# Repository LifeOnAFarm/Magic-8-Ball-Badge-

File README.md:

# Magic 8-Ball Badge 
Created in the lead up to DefCon 26 #BadgeLife

## Getting Started

Welcome to the Magic 8-Ball Badge files/guide.

Here you will find a svg image of the PCB and all the schematics, gerbers and Kicad files you need to make your own Magic 8-Ball Badge. I recommend @MrTwinkleTwink's video on how to convert svg images to Kicad files using Inkscape if you want to make any board chances (https://youtu.be/61NFK9KW).
  
First off, as a warning, I'm by no stretch of the imagination a professional PCB designer and while I have tested the circuit on a similar project I've yet to receive and test this PCB (Will update when I do). Make sure to check through the schematics and make any changes you feel fit (and try not to have an aneurysm when you look at my wiring).

## Quirks:

There are a few quirks to this board. One ~~flaw~~ feature is that the switch doesn't power the PCB on and off, but switches the power from the 8-Ball circuit to the Shitty Add-On headers. Another quirk you might notice in Kicad, is that I couldn't find the footprint for a SW-200D tilt switch so I just used a similar sized component.

## Components You Will Need:

- 1 x SW-200D Tilt Switch

- 3 x 0.1" 2x2 Female Headers

- 8 x 1206 LEDS (Solder these with the top of the LED facing towards the PCB board)

- 1 x Keystone 1058 2032 Coincell Battery Holder

- 1 x CD4017BM Decade counter

- 1 x 0805 10K Resistor

- 1 x 0805 220 Resistor

- 1 x Switch Slide JS202011SCQN 

## Authors

- Seamus de Cleir (@PotatoNightmare)

## License

This project is licensed under the MIT License. 

All I ask is that you leave my Twitter handle on the back of the board, thanks. - see the LICENSE.md file for more details

## Acknowledgments

@MrTwinkleTwink for the great tutorial on SAO's 

## Donations

A button to buy me a cup of coffee if you see fit

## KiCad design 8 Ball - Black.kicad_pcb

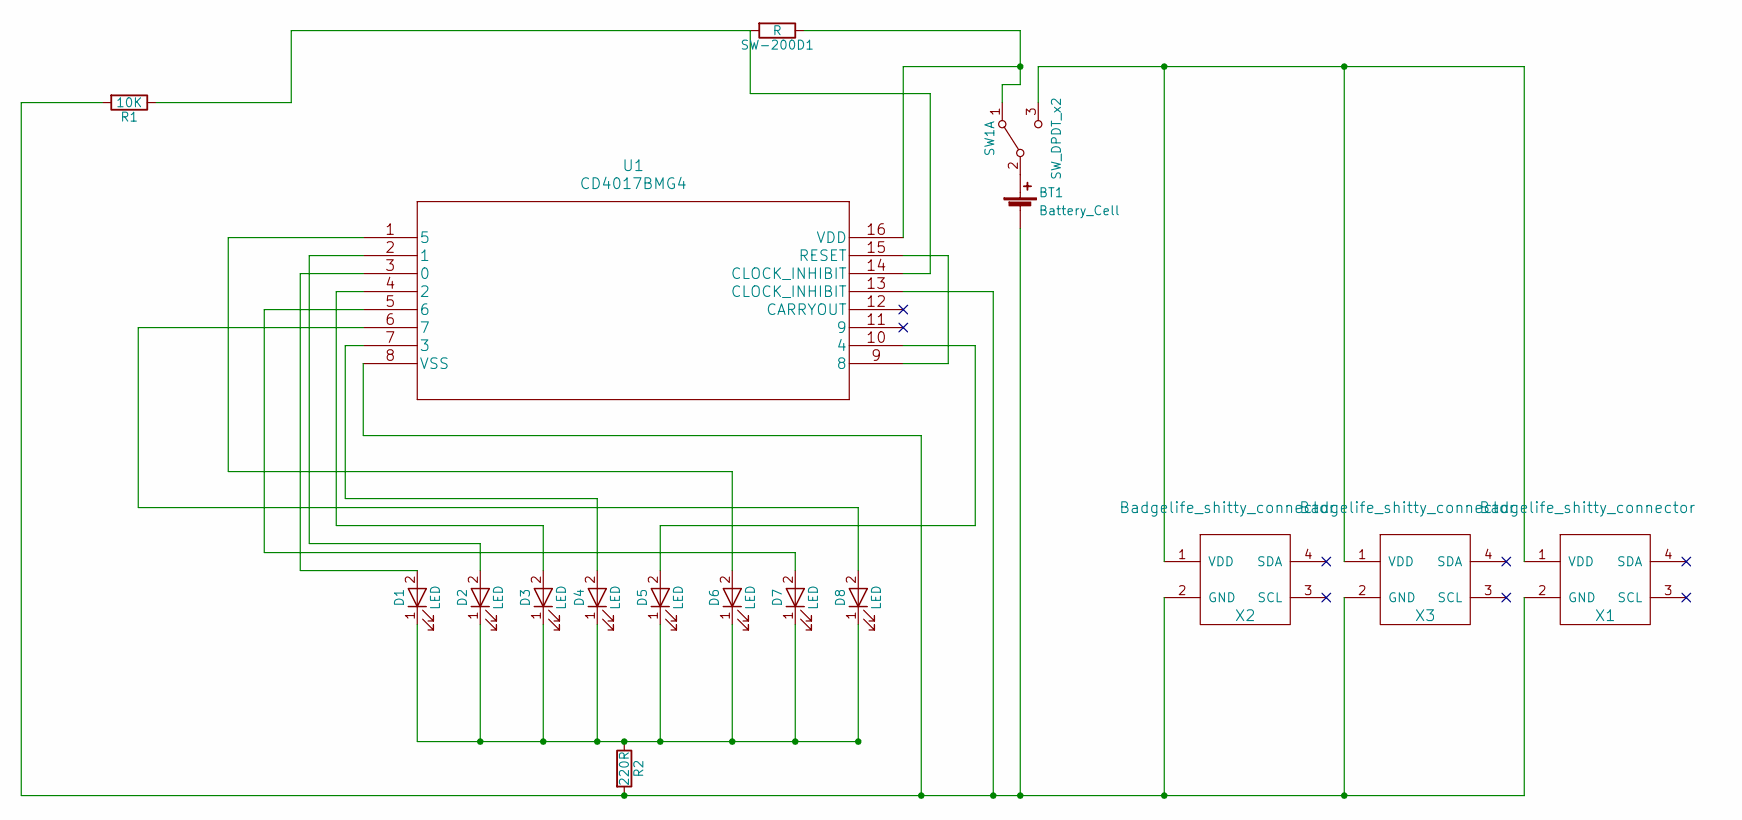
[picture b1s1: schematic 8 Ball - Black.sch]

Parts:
BT1: Battery_Cell; Keystone_1058_1x2032-CoinCell
D1, D2, D3, D4, D5, D6, D7, D8: LED; LED_1206_HandSoldering
R1: 10K; LED_0805_HandSoldering
R2: 220R; LED_0805_HandSoldering
SW1: SW_DPDT_x2; Switch_Slide_JS202011SCQN
SW-200D1: R; CP_Axial_L10.0mm_D4.5mm_P15.00mm_Horizontal
U1: CD4017BMG4; CD4017BM96
X1, X2, X3: Badgelife_shitty_connector; Badgelife-Shitty-2x2

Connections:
unnamed: BT1.1 (+), SW1.2 (B)
unnamed: BT1.2 (-), R1.2, R2.2, U1.8 (VSS), U1.13 (CLOCK_INHIBIT), X1.2 (GND), X2.2 (GND), X3.2 (GND)
unnamed: D1.1 (K), D2.1 (K), D3.1 (K), D4.1 (K), D5.1 (K), D6.1 (K), D7.1 (K), D8.1 (K), R2.1
unnamed: D1.2 (A), U1.3 (0)
unnamed: D2.2 (A), U1.2 (1)
unnamed: D3.2 (A), U1.4 (2)
unnamed: D4.2 (A), U1.7 (3)
unnamed: D5.2 (A), U1.10 (4)
unnamed: D6.2 (A), U1.1 (5)
unnamed: D7.2 (A), U1.5 (6)
unnamed: D8.2 (A), U1.6 (7)
unnamed: R1.1, SW-200D1.2, U1.14 (CLOCK_INHIBIT)
unnamed: SW1.3 (C), X1.1 (VDD), X2.1 (VDD), X3.1 (VDD)
unnamed: SW1.1 (A), SW-200D1.1, U1.16 (VDD)
unnamed: U1.9 (8), U1.15 (RESET)

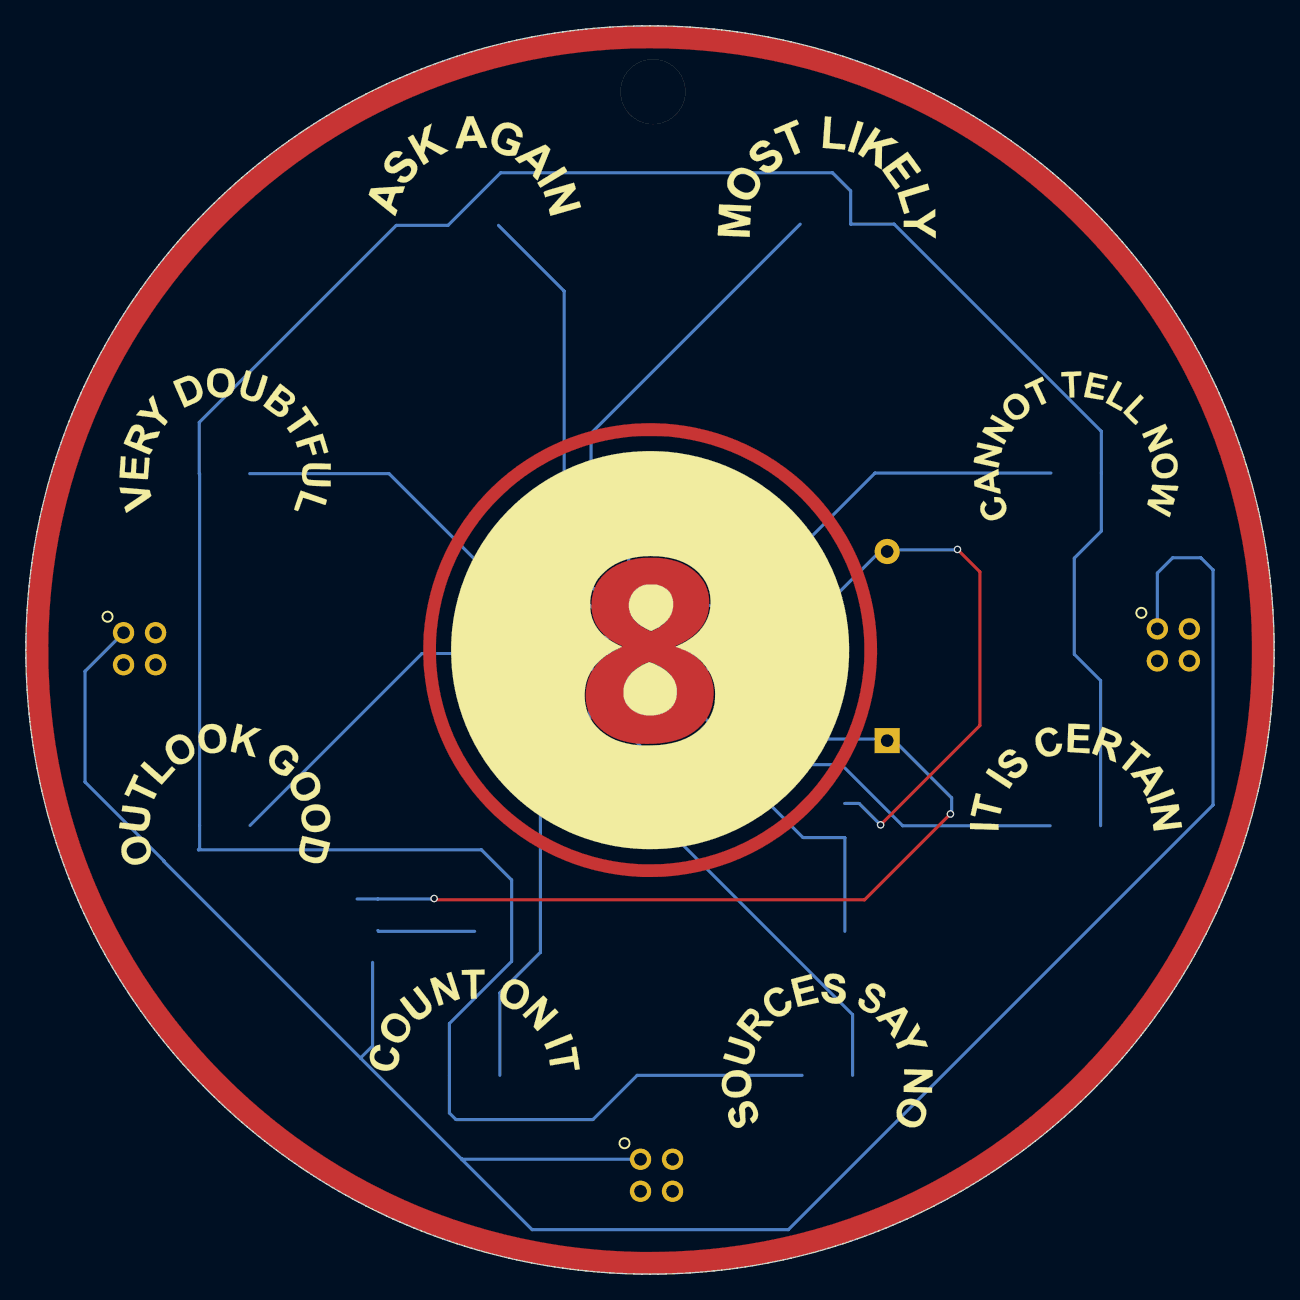
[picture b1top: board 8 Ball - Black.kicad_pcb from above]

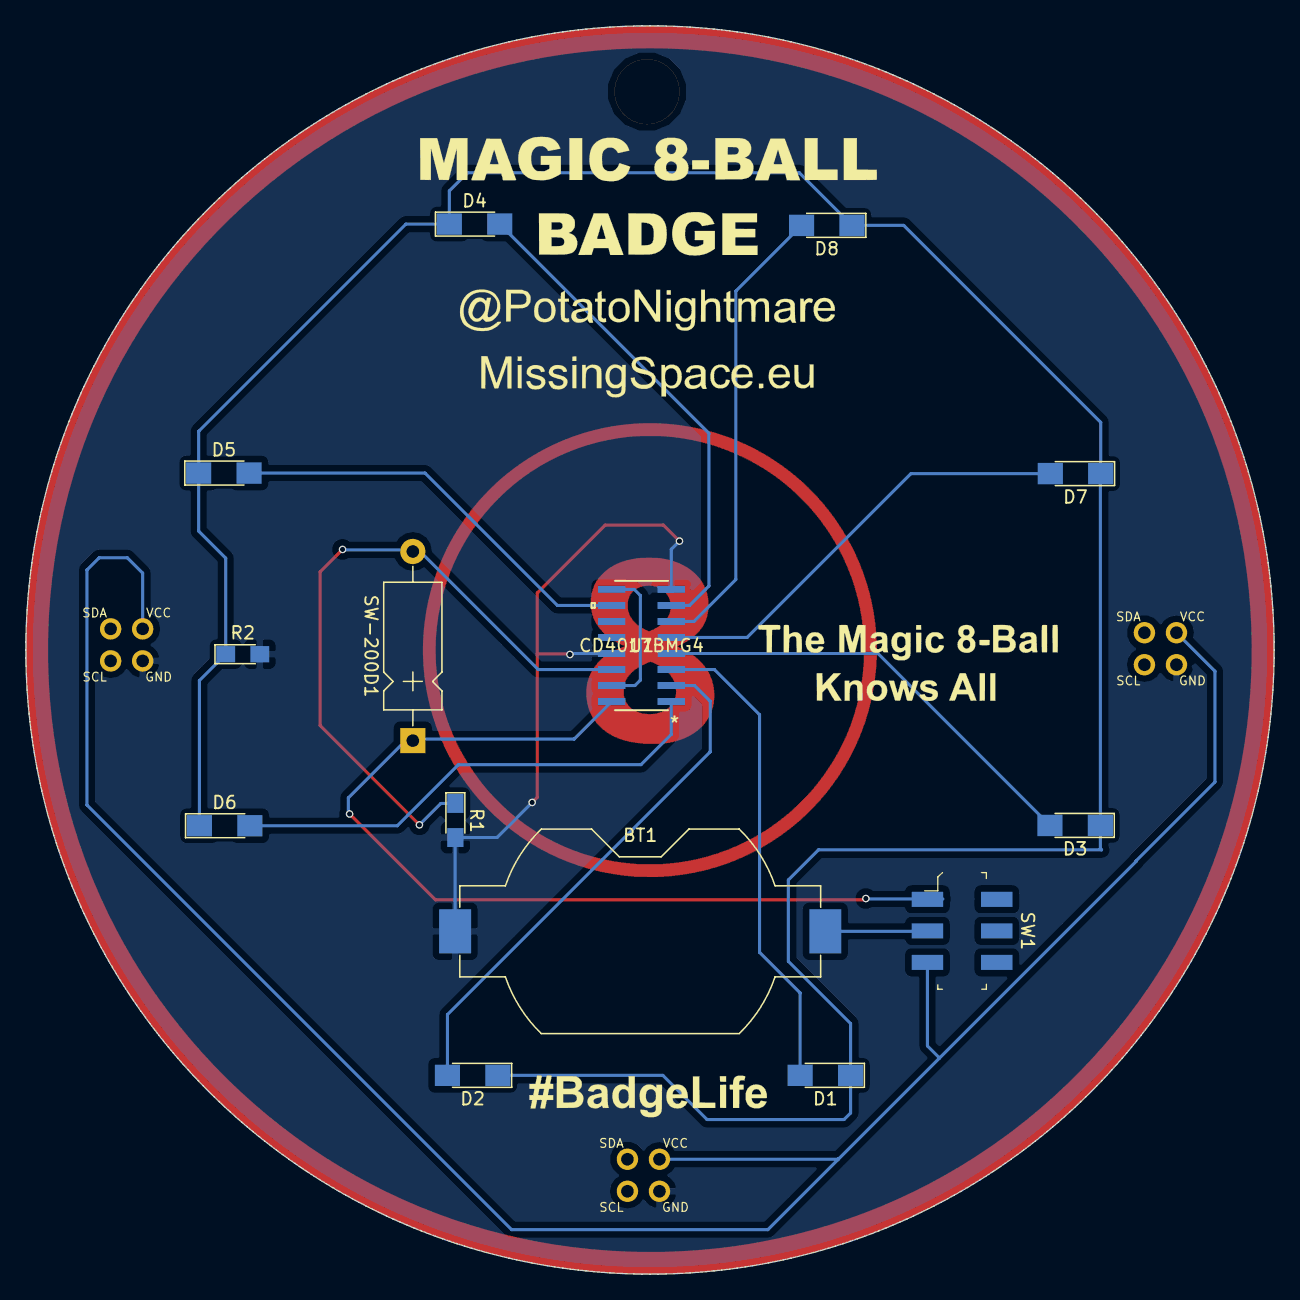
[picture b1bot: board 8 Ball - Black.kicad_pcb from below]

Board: 2 copper layers, 99.0 x 99.0 mm, 17 parts (14 on the bottom side), 15 nets.

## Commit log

2018-07-20 Change
2018-07-20 Image
2018-07-20 Donate
2018-07-20 Read

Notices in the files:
parts and their libraries:
Copyright 2016 Accelerated Designs. All rights reserved.
